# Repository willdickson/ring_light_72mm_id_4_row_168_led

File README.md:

#  ring_light_72mm_id_4_row_168_led

A ring light design with a 72mm ID hole and 168 LED arranged in 4 rows.

# License: 
Creative Commons Attribution 4.0 International CC BY 4.0

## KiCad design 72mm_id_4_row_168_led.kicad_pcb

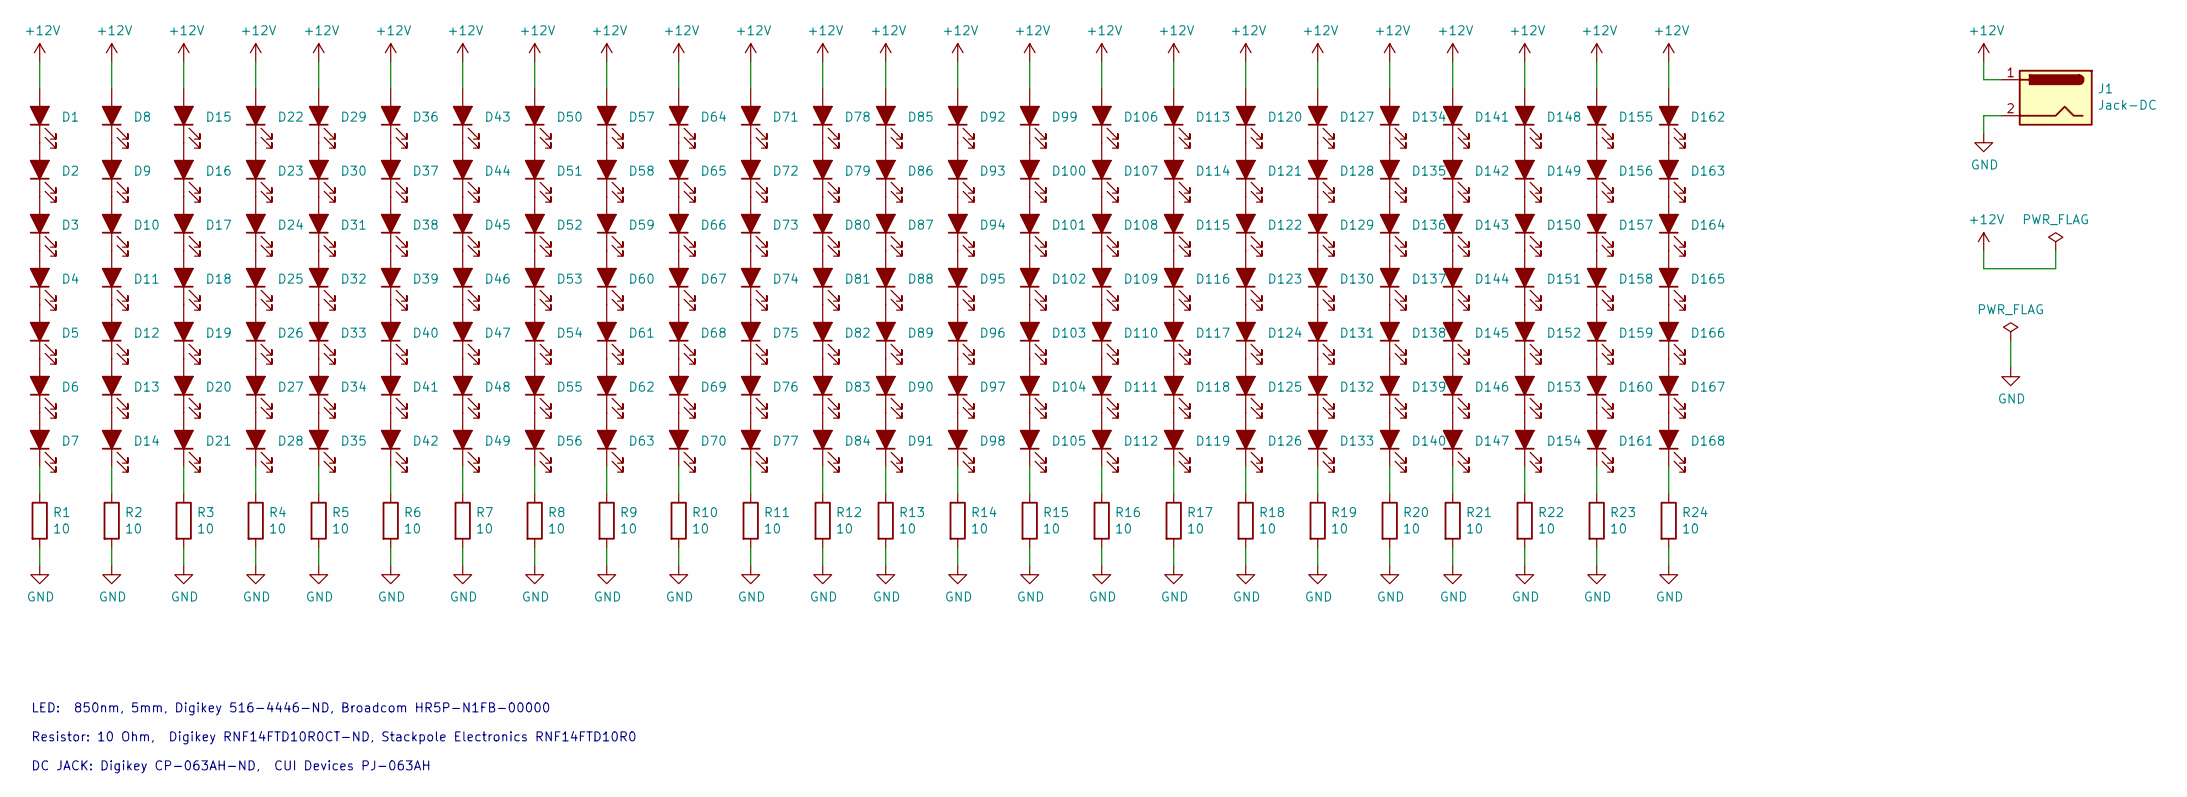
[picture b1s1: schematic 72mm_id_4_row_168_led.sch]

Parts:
D1, D2, D3, D4, D5, D6, D7, D8, D9, D10, D11, D12, D13, D14, D15, D16, D17, D18, D19, D20, D21, D22, D23, D24, D25, D26, D27, D28, D29, D30, D31, D32, D33, D34, D35, D36, D37, D38, D39, D40, D41, D42, D43, D44, D45, D46, D47, D48, D49, D50, D51, D52, D53, D54, D55, D56, D57, D58, D59, D60, D61, D62, D63, D64, D65, D66, D67, D68, D69, D70, D71, D72, D73, D74, D75, D76, D77, D78, D79, D80, D81, D82, D83, D84, D85, D86, D87, D88, D89, D90, D91, D92, D93, D94, D95, D96, D97, D98, D99, D100, D101, D102, D103, D104, D105, D106, D107, D108, D109, D110, D111, D112, D113, D114, D115, D116, D117, D118, D119, D120, D121, D122, D123, D124, D125, D126, D127, D128, D129, D130, D131, D132, D133, D134, D135, D136, D137, D138, D139, D140, D141, D142, D143, D144, D145, D146, D147, D148, D149, D150, D151, D152, D153, D154, D155, D156, D157, D158, D159, D160, D161, D162, D163, D164, D165, D166, D167, D168: LED_ALT; LED_D5mm_centered
J1: Jack-DC; BarrelJack_CUI_PJ-063AH_Horizontal
R1, R2, R3, R4, R5, R6, R7, R8, R9, R10, R11, R12, R13, R14, R15, R16, R17, R18, R19, R20, R21, R22, R23, R24: 10; R_centered

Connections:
+12V: D1.2 (A), D8.2 (A), D15.2 (A), D22.2 (A), D29.2 (A), D36.2 (A), D43.2 (A), D50.2 (A), D57.2 (A), D64.2 (A), D71.2 (A), D78.2 (A), D85.2 (A), D92.2 (A), D99.2 (A), D106.2 (A), D113.2 (A), D120.2 (A), D127.2 (A), D134.2 (A), D141.2 (A), D148.2 (A), D155.2 (A), D162.2 (A), J1.1
GND: J1.2, R1.2, R2.2, R3.2, R4.2, R5.2, R6.2, R7.2, R8.2, R9.2, R10.2, R11.2, R12.2, R13.2, R14.2, R15.2, R16.2, R17.2, R18.2, R19.2, R20.2, R21.2, R22.2, R23.2, R24.2
unnamed: D1.1 (K), D2.2 (A)
unnamed: D2.1 (K), D3.2 (A)
unnamed: D3.1 (K), D4.2 (A)
unnamed: D4.1 (K), D5.2 (A)
unnamed: D5.1 (K), D6.2 (A)
unnamed: D6.1 (K), D7.2 (A)
unnamed: D7.1 (K), R1.1
unnamed: D8.1 (K), D9.2 (A)
unnamed: D10.1 (K), D11.2 (A)
unnamed: D9.1 (K), D10.2 (A)
unnamed: D11.1 (K), D12.2 (A)
unnamed: D12.1 (K), D13.2 (A)
unnamed: D13.1 (K), D14.2 (A)
unnamed: D14.1 (K), R2.1
unnamed: D15.1 (K), D16.2 (A)
unnamed: D16.1 (K), D17.2 (A)
unnamed: D17.1 (K), D18.2 (A)
unnamed: D18.1 (K), D19.2 (A)
unnamed: D19.1 (K), D20.2 (A)
unnamed: D20.1 (K), D21.2 (A)
unnamed: D21.1 (K), R3.1
unnamed: D22.1 (K), D23.2 (A)
unnamed: D23.1 (K), D24.2 (A)
unnamed: D24.1 (K), D25.2 (A)
unnamed: D25.1 (K), D26.2 (A)
unnamed: D26.1 (K), D27.2 (A)
unnamed: D27.1 (K), D28.2 (A)
unnamed: D28.1 (K), R4.1
unnamed: D29.1 (K), D30.2 (A)
unnamed: D30.1 (K), D31.2 (A)
unnamed: D31.1 (K), D32.2 (A)
unnamed: D32.1 (K), D33.2 (A)
unnamed: D33.1 (K), D34.2 (A)
unnamed: D34.1 (K), D35.2 (A)
unnamed: D35.1 (K), R5.1
unnamed: D36.1 (K), D37.2 (A)
unnamed: D37.1 (K), D38.2 (A)
unnamed: D38.1 (K), D39.2 (A)
unnamed: D39.1 (K), D40.2 (A)
unnamed: D40.1 (K), D41.2 (A)
unnamed: D41.1 (K), D42.2 (A)
unnamed: D42.1 (K), R6.1
unnamed: D43.1 (K), D44.2 (A)
unnamed: D44.1 (K), D45.2 (A)
unnamed: D45.1 (K), D46.2 (A)
unnamed: D46.1 (K), D47.2 (A)
unnamed: D47.1 (K), D48.2 (A)
unnamed: D48.1 (K), D49.2 (A)
unnamed: D49.1 (K), R7.1
unnamed: D50.1 (K), D51.2 (A)
unnamed: D51.1 (K), D52.2 (A)
unnamed: D52.1 (K), D53.2 (A)
unnamed: D53.1 (K), D54.2 (A)
unnamed: D54.1 (K), D55.2 (A)
unnamed: D55.1 (K), D56.2 (A)
unnamed: D56.1 (K), R8.1
unnamed: D57.1 (K), D58.2 (A)
unnamed: D58.1 (K), D59.2 (A)
unnamed: D59.1 (K), D60.2 (A)
unnamed: D60.1 (K), D61.2 (A)
unnamed: D61.1 (K), D62.2 (A)
unnamed: D62.1 (K), D63.2 (A)
unnamed: D63.1 (K), R9.1
unnamed: D64.1 (K), D65.2 (A)
unnamed: D65.1 (K), D66.2 (A)
unnamed: D66.1 (K), D67.2 (A)
unnamed: D67.1 (K), D68.2 (A)
unnamed: D68.1 (K), D69.2 (A)
unnamed: D69.1 (K), D70.2 (A)
unnamed: D70.1 (K), R10.1
unnamed: D71.1 (K), D72.2 (A)
unnamed: D72.1 (K), D73.2 (A)
unnamed: D73.1 (K), D74.2 (A)
unnamed: D74.1 (K), D75.2 (A)
unnamed: D75.1 (K), D76.2 (A)
unnamed: D76.1 (K), D77.2 (A)
unnamed: D77.1 (K), R11.1
unnamed: D78.1 (K), D79.2 (A)
unnamed: D79.1 (K), D80.2 (A)
unnamed: D80.1 (K), D81.2 (A)
unnamed: D81.1 (K), D82.2 (A)
unnamed: D82.1 (K), D83.2 (A)
unnamed: D83.1 (K), D84.2 (A)
unnamed: D84.1 (K), R12.1
unnamed: D85.1 (K), D86.2 (A)
unnamed: D86.1 (K), D87.2 (A)
unnamed: D87.1 (K), D88.2 (A)
unnamed: D88.1 (K), D89.2 (A)
unnamed: D89.1 (K), D90.2 (A)
unnamed: D90.1 (K), D91.2 (A)
unnamed: D91.1 (K), R13.1
unnamed: D92.1 (K), D93.2 (A)
unnamed: D93.1 (K), D94.2 (A)
unnamed: D94.1 (K), D95.2 (A)
unnamed: D95.1 (K), D96.2 (A)
unnamed: D96.1 (K), D97.2 (A)
unnamed: D97.1 (K), D98.2 (A)
unnamed: D98.1 (K), R14.1
unnamed: D100.1 (K), D101.2 (A)
unnamed: D99.1 (K), D100.2 (A)
unnamed: D101.1 (K), D102.2 (A)
unnamed: D102.1 (K), D103.2 (A)
unnamed: D103.1 (K), D104.2 (A)
unnamed: D104.1 (K), D105.2 (A)
unnamed: D105.1 (K), R15.1
unnamed: D106.1 (K), D107.2 (A)
unnamed: D107.1 (K), D108.2 (A)
unnamed: D108.1 (K), D109.2 (A)
unnamed: D109.1 (K), D110.2 (A)
unnamed: D110.1 (K), D111.2 (A)
unnamed: D111.1 (K), D112.2 (A)
unnamed: D112.1 (K), R16.1
unnamed: D113.1 (K), D114.2 (A)
unnamed: D114.1 (K), D115.2 (A)
unnamed: D115.1 (K), D116.2 (A)
unnamed: D116.1 (K), D117.2 (A)
unnamed: D117.1 (K), D118.2 (A)
unnamed: D118.1 (K), D119.2 (A)
unnamed: D119.1 (K), R17.1
unnamed: D120.1 (K), D121.2 (A)
unnamed: D121.1 (K), D122.2 (A)
unnamed: D122.1 (K), D123.2 (A)
unnamed: D123.1 (K), D124.2 (A)
unnamed: D124.1 (K), D125.2 (A)
unnamed: D125.1 (K), D126.2 (A)
unnamed: D126.1 (K), R18.1
unnamed: D127.1 (K), D128.2 (A)
unnamed: D128.1 (K), D129.2 (A)
unnamed: D129.1 (K), D130.2 (A)
unnamed: D130.1 (K), D131.2 (A)
unnamed: D131.1 (K), D132.2 (A)
unnamed: D132.1 (K), D133.2 (A)
unnamed: D133.1 (K), R19.1
unnamed: D134.1 (K), D135.2 (A)
unnamed: D135.1 (K), D136.2 (A)
unnamed: D136.1 (K), D137.2 (A)
unnamed: D137.1 (K), D138.2 (A)
unnamed: D138.1 (K), D139.2 (A)
unnamed: D139.1 (K), D140.2 (A)
unnamed: D140.1 (K), R20.1
unnamed: D141.1 (K), D142.2 (A)
unnamed: D142.1 (K), D143.2 (A)
unnamed: D143.1 (K), D144.2 (A)
unnamed: D144.1 (K), D145.2 (A)
unnamed: D145.1 (K), D146.2 (A)
unnamed: D146.1 (K), D147.2 (A)
unnamed: D147.1 (K), R21.1
unnamed: D148.1 (K), D149.2 (A)
unnamed: D149.1 (K), D150.2 (A)
unnamed: D150.1 (K), D151.2 (A)
unnamed: D151.1 (K), D152.2 (A)
unnamed: D152.1 (K), D153.2 (A)
unnamed: D153.1 (K), D154.2 (A)
unnamed: D154.1 (K), R22.1
unnamed: D155.1 (K), D156.2 (A)
unnamed: D156.1 (K), D157.2 (A)
unnamed: D157.1 (K), D158.2 (A)
unnamed: D158.1 (K), D159.2 (A)
unnamed: D159.1 (K), D160.2 (A)
unnamed: D160.1 (K), D161.2 (A)
unnamed: D161.1 (K), R23.1
unnamed: D162.1 (K), D163.2 (A)
unnamed: D163.1 (K), D164.2 (A)
unnamed: D164.1 (K), D165.2 (A)
unnamed: D165.1 (K), D166.2 (A)
unnamed: D166.1 (K), D167.2 (A)
unnamed: D167.1 (K), D168.2 (A)
unnamed: D168.1 (K), R24.1

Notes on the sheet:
LED: 850nm, 5mm, Digikey 516-4446-ND, Broadcom HR5P-N1FB-00000 Resistor: 10 Ohm, Digikey RNF14FTD10R0CT-ND, Stackpole Electronics RNF14FTD10R0 DC JACK: Digikey CP-063AH-ND, CUI Devices PJ-063AH

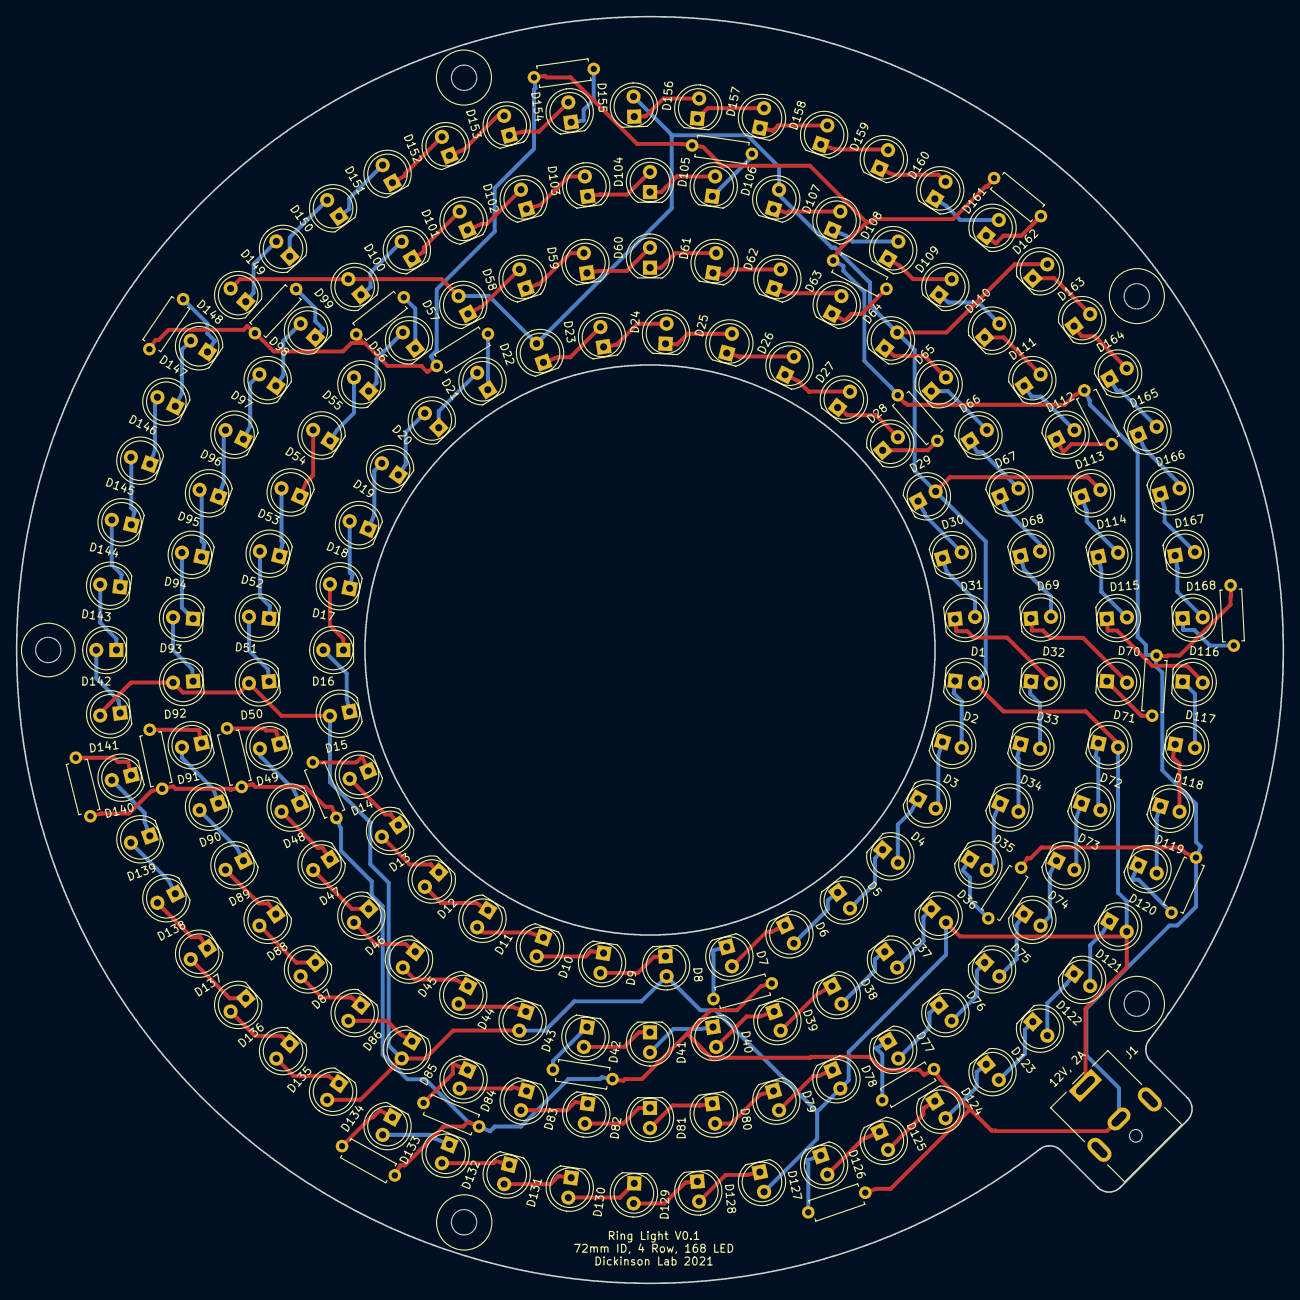
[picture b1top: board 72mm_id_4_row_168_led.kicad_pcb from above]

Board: 2 copper layers, 160.0 x 160.0 mm, 198 parts (0 on the bottom side), 170 nets.

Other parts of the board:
M1, M2, M3, M4, M5: MountingHole_3.2mm_M3

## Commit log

2021-06-02 Project creation.
2021-06-02 Added link to image in README.
2021-06-02 Fixed typo in readme.
